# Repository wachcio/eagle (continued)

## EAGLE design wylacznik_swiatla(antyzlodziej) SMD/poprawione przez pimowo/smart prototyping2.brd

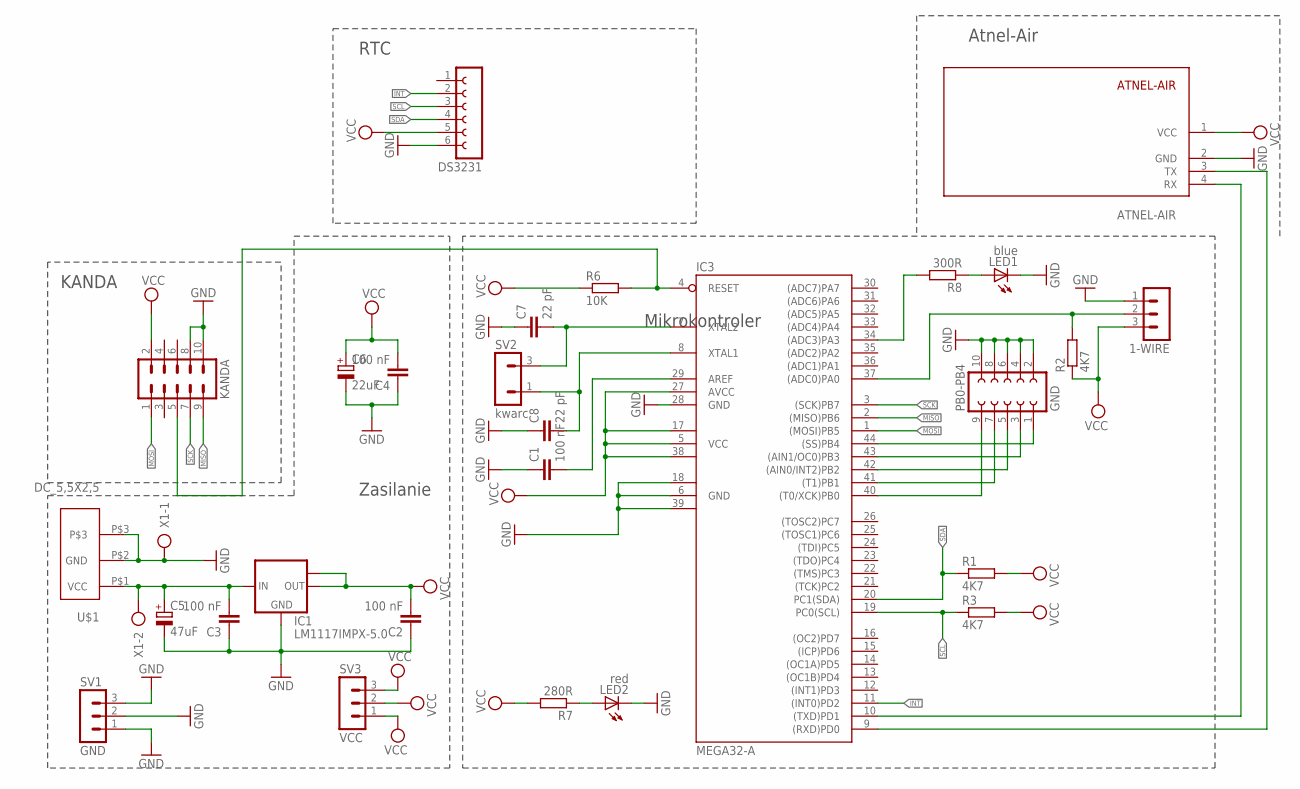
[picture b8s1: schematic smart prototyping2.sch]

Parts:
1-WIRE: MA03-1
ATNEL-AIR: ATNEL-AIR
C1, C2, C3, C4: 100 nF; C0805
C5: 47uF; B45181A
C6: 22uF; B45181A
C7, C8: 22 pF; C0805
DS3231: FE06-1; FE06
IC1: LM1117IMPX-5.0; SOT223
IC3: MEGA32-A; TQFP44
KANDA: ML10
LED1: blue; CHIPLED_1206
LED2: red; CHIPLED_1206
PB0-PB4: GND; FE05-2
R1, R2, R3: 4K7; R1206W
R6: 10K; R1206W
R7: 280R; R1206W
R8: 300R; R1206W
SV1: GND; MA03-1
SV2: kwarc; MA03-1
SV3: VCC; MA03-1
U$1: DC_5,5X2,5
X1: AK500/2

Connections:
GND: 1-WIRE.1, ATNEL-AIR.2 (GND), C1.1, C2.1, C3.1, C4.1, C5.-, C6.-, C7.1, C8.1, DS3231.6, IC1.1 (GND), IC3.6 (GND), IC3.18 (GND1), IC3.28 (GND), IC3.39 (GND2), KANDA.8, KANDA.10, LED1.C, LED2.C, PB0-PB4.2, PB0-PB4.4, PB0-PB4.6, PB0-PB4.8, PB0-PB4.10, SV1.1, SV1.2, SV1.3, U$1.P$2 (GND), U$1.P$3, X1.1
INT: DS3231.2, IC3.11 ((INT0)PD2)
MISO: IC3.2 ((MISO)PB6), KANDA.9
MOSI: IC3.1 ((MOSI)PB5), KANDA.1
unnamed: ATNEL-AIR.4 (RX), IC3.10 ((TXD)PD1)
unnamed: ATNEL-AIR.3 (TX), IC3.9 ((RXD)PD0)
unnamed: C1.2, IC3.29 (AREF)
unnamed: IC3.44 ((SS)PB4), PB0-PB4.1
unnamed: IC3.43 ((AIN1/OC0)PB3), PB0-PB4.3
unnamed: C3.2, C5.+, IC1.3 (IN), U$1.P$1 (VCC), X1.2
unnamed: IC3.42 ((AIN0/INT2)PB2), PB0-PB4.5
unnamed: IC3.41 ((T1)PB1), PB0-PB4.7
unnamed: IC3.40 ((T0/XCK)PB0), PB0-PB4.9
unnamed: C7.2, IC3.7 (XTAL2), SV2.3
unnamed: C8.2, IC3.8 (XTAL1), SV2.1
unnamed: LED2.A, R7.1
unnamed: LED1.A, R8.1
unnamed: IC3.34 ((ADC3)PA3), R8.2
unnamed: 1-WIRE.2, IC3.37 ((ADC0)PA0), R2.2
RST: IC3.4 (RESET), KANDA.5, R6.2
SCK: IC3.3 ((SCK)PB7), KANDA.7
SCL: DS3231.3, IC3.19 (PC0(SCL)), R3.1
SDA: DS3231.4, IC3.20 (PC1(SDA)), R1.1
VCC: 1-WIRE.3, ATNEL-AIR.1 (VCC), C2.2, C4.2, C6.+, DS3231.5, IC1.2 (OUT), IC1.TAB (OUT1), IC3.5 (VCC), IC3.17 (VCC1), IC3.27 (AVCC), IC3.38 (VCC2), KANDA.2, R1.2, R2.1, R3.2, R6.1, R7.2, SV3.1, SV3.2, SV3.3

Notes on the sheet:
Atnel-Air
KANDA
RTC
Zasilanie
Mikrokontroler

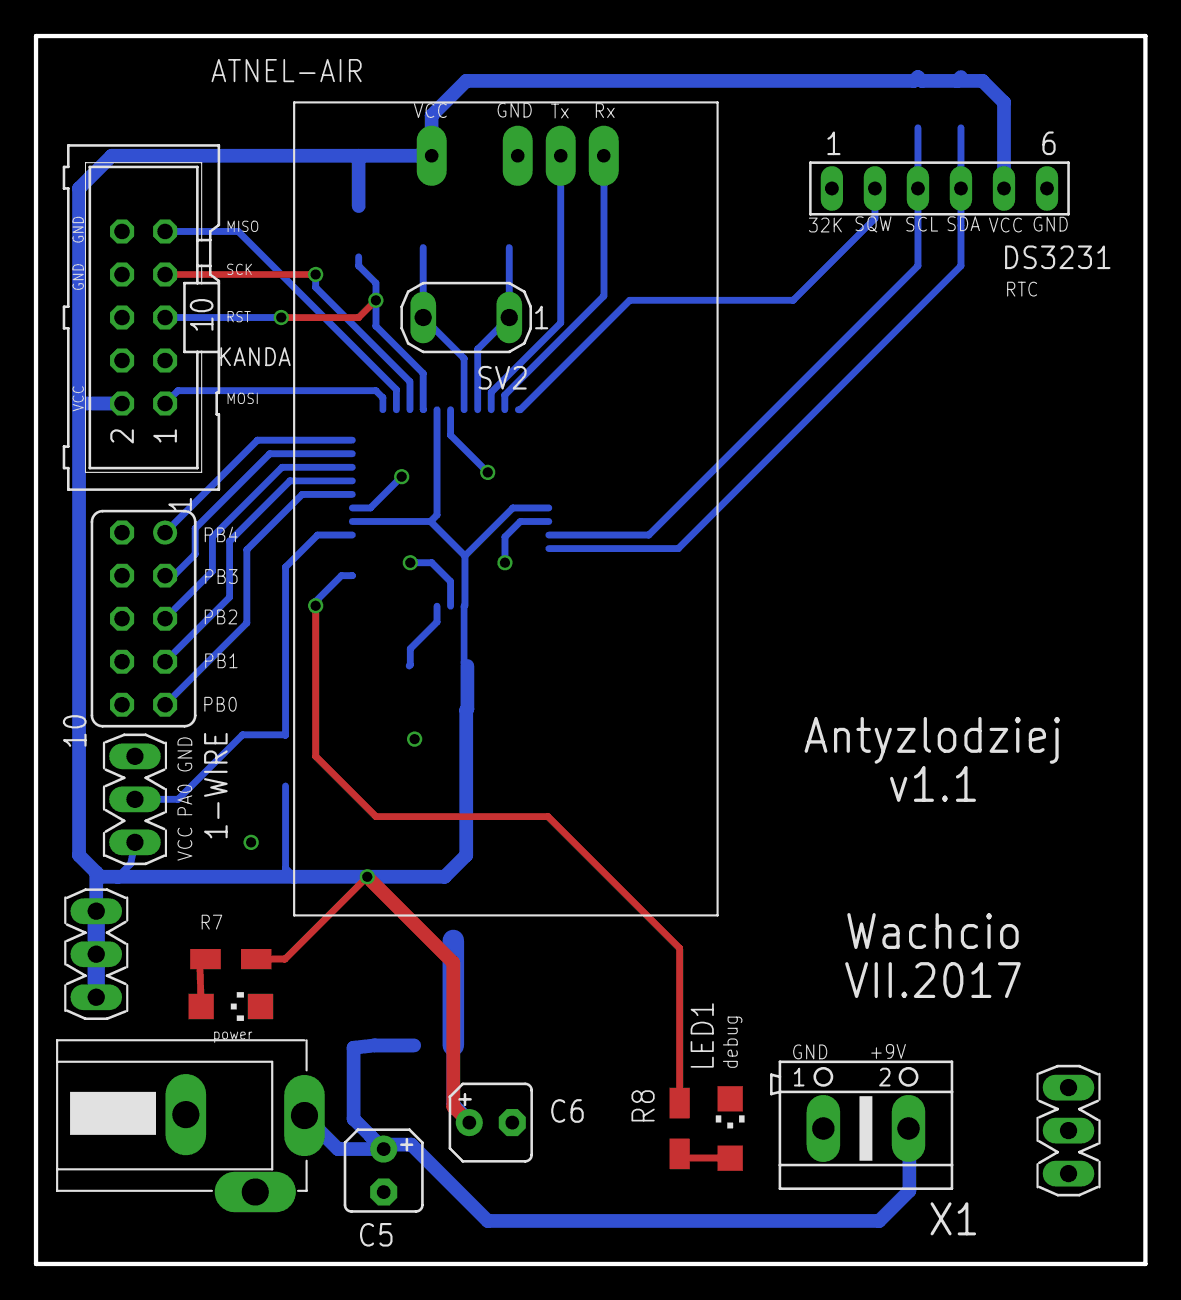
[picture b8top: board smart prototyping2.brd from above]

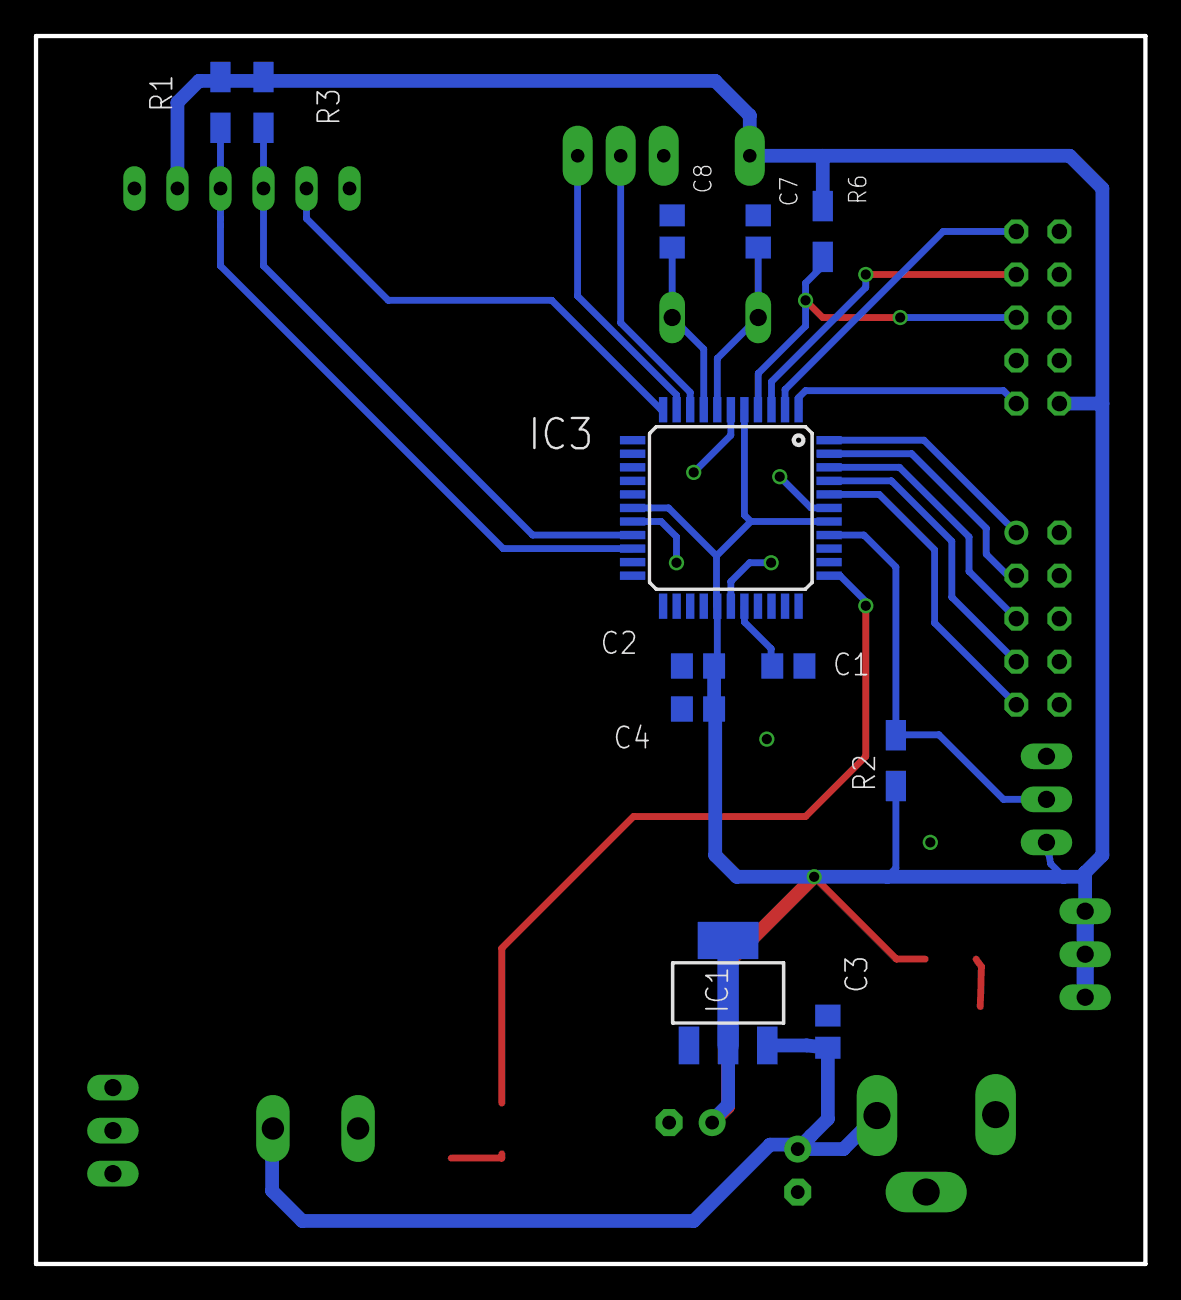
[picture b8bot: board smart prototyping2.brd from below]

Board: 2 copper layers, 65.5 x 72.5 mm, 28 parts (12 on the bottom side), 24 nets.
